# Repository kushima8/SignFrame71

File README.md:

# SignFrame71
A keyboard inspired by the SignFrame from Horizon on the Middle of Nowhere.

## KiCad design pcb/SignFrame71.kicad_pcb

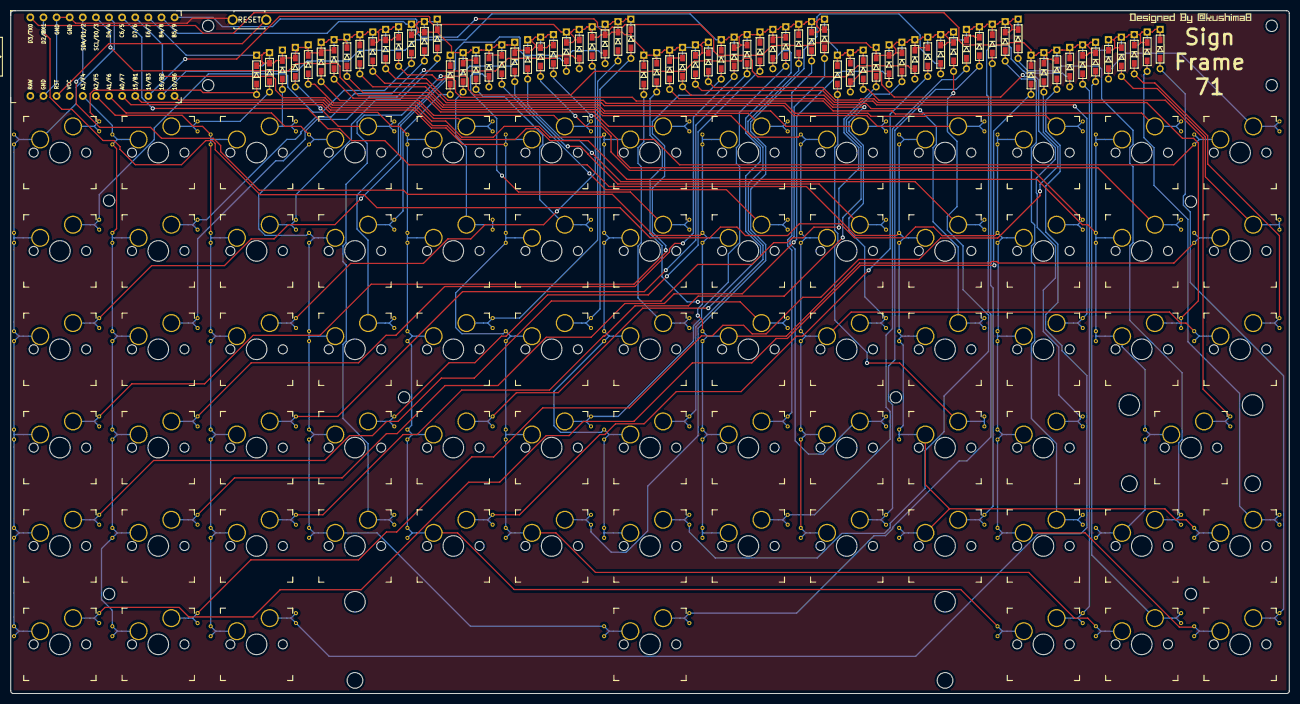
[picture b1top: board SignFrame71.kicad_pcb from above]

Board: 2 copper layers, 247.7 x 132.3 mm, 156 parts (0 on the bottom side), 91 nets.

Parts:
D1, D2, D3, D4, D5, D6, D7, D8, D9, D10, D11, D12, D13, D14, D15, D16, D17, D18, D19, D20, D21, D22, D23, D24, D25, D26, D27, D28, D29, D30, D31, D32, D33, D34, D35, D36, D37, D38, D39, D40, D41, D42, D43, D44, D45, D46, D47, D48, D49, D50, D51, D52, D53, D54, D55, D56, D57, D58, D59, D60, D61, D62, D63, D64, D65, D66, D67, D68, D69, D70, D71: D; D3_TH_SMD
REF1, REF2, REF3, REF4, REF5, REF6, REF7, REF8, REF9, REF10: MountingHole_2.2mm_M2
REF01: 7U; MX-7U
REF02: 2U; MX-2U
SW1, SW2, SW3, SW4, SW5, SW6, SW7, SW8, SW9, SW10, SW11, SW12, SW13, SW14, SW15, SW16, SW17, SW18, SW19, SW20, SW21, SW22, SW23, SW24, SW25, SW26, SW27, SW28, SW29, SW30, SW31, SW32, SW33, SW34, SW35, SW36, SW37, SW38, SW39, SW40, SW41, SW42, SW43, SW44, SW45, SW46, SW47, SW48, SW49, SW50, SW51, SW52, SW53, SW54, SW55, SW56, SW57, SW58, SW59, SW60, SW61, SW62, SW63, SW64, SW65, SW66, SW67, SW68, SW69, SW70, SW71: SW_PUSH; CherryMX_Hotswap_v2
SW72: SW_PUSH; ResetSW_1side
U1: ProMicro; ProMicro_v3.5

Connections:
GND: SW72.2, U1.3, U1.4, U1.23
unnamed: D1.2, SW1.2
unnamed: D2.2, SW2.2
unnamed: D3.2, SW3.2
unnamed: D4.2, SW4.2
unnamed: D5.2, SW5.2
unnamed: D6.2, SW6.2
unnamed: D7.2, SW7.2
unnamed: D8.2, SW8.2
unnamed: D9.2, SW9.2
unnamed: D10.2, SW10.2
unnamed: D11.2, SW11.2
unnamed: D12.2, SW12.2
unnamed: D13.2, SW13.2
unnamed: D14.2, SW14.2
unnamed: D15.2, SW15.2
unnamed: D16.2, SW16.2
unnamed: D17.2, SW17.2
unnamed: D18.2, SW18.2
unnamed: D19.2, SW19.2
unnamed: D20.2, SW20.2
unnamed: D21.2, SW21.2
unnamed: D22.2, SW22.2
unnamed: D23.2, SW23.2
unnamed: D24.2, SW24.2
unnamed: D25.2, SW25.2
unnamed: D26.2, SW26.2
unnamed: D27.2, SW27.2
unnamed: D28.2, SW28.2
unnamed: D29.2, SW29.2
unnamed: D30.2, SW30.2
unnamed: D31.2, SW31.2
unnamed: D32.2, SW32.2
unnamed: D33.2, SW33.2
unnamed: D34.2, SW34.2
unnamed: D35.2, SW35.2
unnamed: D36.2, SW36.2
unnamed: D37.2, SW37.2
unnamed: D38.2, SW38.2
unnamed: D39.2, SW39.2
unnamed: D40.2, SW40.2
unnamed: D41.2, SW41.2
unnamed: D42.2, SW42.2
unnamed: D43.2, SW43.2
unnamed: D44.2, SW44.2
unnamed: D45.2, SW45.2
unnamed: D46.2, SW46.2
unnamed: D47.2, SW47.2
unnamed: D48.2, SW48.2
unnamed: D49.2, SW49.2
unnamed: D50.2, SW50.2
unnamed: D51.2, SW51.2
unnamed: D52.2, SW52.2
unnamed: D53.2, SW53.2
unnamed: D54.2, SW54.2
unnamed: D55.2, SW55.2
unnamed: D56.2, SW56.2
unnamed: D57.2, SW57.2
unnamed: D58.2, SW58.2
unnamed: D59.2, SW59.2
unnamed: D60.2, SW60.2
unnamed: D61.2, SW61.2
unnamed: D62.2, SW62.2
unnamed: D63.2, SW63.2
unnamed: D64.2, SW64.2
unnamed: D65.2, SW65.2
unnamed: D66.2, SW66.2
unnamed: D67.2, SW67.2
unnamed: D68.2, SW68.2
unnamed: D69.2, SW69.2
unnamed: D70.2, SW70.2
unnamed: D71.2, SW71.2
col0: SW1.1, SW13.1, SW25.1, SW37.1, SW49.1, SW61.1, U1.7
col1: SW2.1, SW14.1, SW26.1, SW38.1, SW50.1, SW62.1, U1.20
col2: SW3.1, SW15.1, SW27.1, SW39.1, SW51.1, SW63.1, U1.19
col3: SW4.1, SW16.1, SW28.1, SW40.1, SW52.1, SW64.1, U1.18
col4: SW5.1, SW17.1, SW29.1, SW41.1, SW53.1, SW65.1, U1.17
col5: SW6.1, SW18.1, SW30.1, SW42.1, SW54.1, SW66.1, U1.16
col6: SW7.1, SW19.1, SW31.1, SW43.1, SW55.1, SW67.1, U1.9
col7: SW8.1, SW20.1, SW32.1, SW44.1, SW56.1, SW68.1, U1.5
col8: SW9.1, SW21.1, SW33.1, SW45.1, SW57.1, SW69.1, U1.6
col9: SW10.1, SW22.1, SW34.1, SW46.1, SW58.1, SW70.1, U1.8
col10: SW11.1, SW23.1, SW35.1, SW47.1, SW59.1, SW71.1, U1.2
col11: SW12.1, SW24.1, SW36.1, SW48.1, SW60.1, U1.13
reset: SW72.1, U1.22
row0: D1.1, D2.1, D3.1, D4.1, D5.1, D6.1, D7.1, D8.1, D9.1, D10.1, D11.1, D12.1, U1.10
row1: D13.1, D14.1, D15.1, D16.1, D17.1, D18.1, D19.1, D20.1, D21.1, D22.1, D23.1, D24.1, U1.11
row2: D25.1, D26.1, D27.1, D28.1, D29.1, D30.1, D31.1, D32.1, D33.1, D34.1, D35.1, D36.1, U1.15
row3: D37.1, D38.1, D39.1, D40.1, D41.1, D42.1, D43.1, D44.1, D45.1, D46.1, D47.1, D48.1, U1.14
row4: D49.1, D50.1, D51.1, D52.1, D53.1, D54.1, D55.1, D56.1, D57.1, D58.1, D59.1, D60.1, U1.12
row5: D61.1, D62.1, D63.1, D64.1, D65.1, D66.1, D67.1, D68.1, D69.1, D70.1, D71.1, U1.1

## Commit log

2021-12-11 Create PCB
